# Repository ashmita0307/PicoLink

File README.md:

# PicoLink
An RP2040-based project for VGA graphics generation and USB composite device implementation.

## Table of Contents

  - [PicoLink](#picolink)
  - [Table of Contents](#table-of-contents)
  - [About The Project](#about-the-project)
  - [Features](#features)
  - [Project Workflow](#project-workflow)
  - [Hardware Used](#hardware-used)
  - [Breadboard Testing](#breadboard-testing)
  - [PCB Model](#pcb-model)
  - [Software Used](#software-used)
  - [Future Work](#future-work)
  - [Contributors](#contributors)
  - [Resources](#resources)
  - [Acknowledgements](#acknowledgements)

## About The Project
**PicoLink** is an RP2040-based project focused on **VGA graphics generation** and **USB communication**. It uses **PIO and DMA** for efficient VGA output and implements a **USB composite device with HID and CDC interfaces**.

## Features

- VGA output using RP2040
- Custom VGA graphics library
- Increased color support
- PIO-based VGA signal generation
- DMA-assisted data transfer
- Custom PCB design
- Space Invaders game
- Pacman game
## Project Workflow

#### Research

* Understanding VGA standards, timing, and signal generation
* Studying the RP2040's PIO and DMA peripherals
* Reviewing existing VGA libraries and RP2040 implementations

#### VGA Graphics Development

* Implementing VGA signal generation using PIO
* Developing a custom VGA graphics library
* Implementing framebuffer-based graphics
* Increasing color support and optimizing memory usage
* Testing VGA output on a monitor

#### PCB Design

* Designing the PicoLink PCB around the RP2040
* Designing the VGA interface and USB connections
* Routing the PCB while considering signal integrity and hardware constraints
* Finalizing the PCB for manufacturing
#### USB Development

* Implementing USB HID functionality
* Implementing USB CDC communication
* Creating and understanding the required USB descriptors
* Integrating HID and CDC as a composite USB device

#### Game Development & Testing

* Developing **Sngpace Invaders & Pacman** using the custom VGA graphics library
* Integrating the game with the PicoLink hardware
* Testing VGA output, USB communication, and overall system performance
* Debugging and optimizing the final implementation

## Hardware Used

|     Components        |          Description          |
| --------------------- | ----------------------------- |
| [RP2040-Mitrocontroller](https://robu.in/product/raspberry-pi-pico/?gad_source=1&gad_campaignid=19974686076&gbraid=0AAAAADvLFWc_9GsTRABB0vDtC2DQhwOhp&gclid=CjwKCAjwqJXUBhBNEiwA8BgG7vailV2Hy5Y_-Ko3vAaZAEXPT5CyTGmnKPxanKmfuWqEnSS08VfShBoCNk0QAvD_BwE)           | Microcontroller |
| [15-Pin VGA Connector](https://robu.in/product/x0615ft7b1-xkb-15p-female-d-sub-3-d-sub-vga-connectors-rohs/)  | VGA-connector |
| [33O ohm Resistors](https://robu.in/product/330-ohm-1-4w-1206-surface-mount-chip-resistor-pack-of-100/?gad_source=1&gad_campaignid=17427802703&gbraid=0AAAAADvLFWfZ2mYmii2USnEMQ98Oe9FQ_&gclid=CjwKCAjwqJXUBhBNEiwA8BgG7kQjg_4zEpnGfV_3AsnYPpfzbiUg2oPFK-0IBOd3eiSTI_ayuLDsIhoC2dwQAvD_BwE/) | Resistor |

## Breadboard Testing
- View of Breadboard VGA Connections:   

## PCB Model

- View of the PCB Model front and back:       
<table>
  <tr>
    <td align="center">
      
    </td>
    <td align="center">
      
    </td>
  </tr>
</table>

- View of the PCB Routing - front and back:      

<table>
  <tr>
    <td align="center">
      
    </td>
    <td align="center">
      
    </td>
  </tr>
</table>

## Software Used 

- PCB Design - [KiCad 10.0.5](https://www.kicad.org/)
- Software development kit for RP2040 - [Raspberry Pi Pico SDK](https://github.com/raspberrypi/pico-sdk) 

## Future Work
- [ ] Develop a more memory-efficient rendering system
- [ ] Develop more games/examples using the custom graphics library

## Contributors
- [Ashmita Subramanian](https://github.com/ashmita0307)
- [Mohd Aasim](https://github.com/Mohdaasim18)

## Resources

- [razorArnov Github Repository](https://github.com/razorArnov/PICO-VGA-BOARD.git)
- [Phil's lab Kicad Playlist](https://www.youtube.com/watch?v=O-zNn5k5Bn4)
- [Mikeshah's C Programming playlist](https://www.youtube.com/playlist?list=PLvv0ScY6vfd8M-Mi_Vyrg7KgISTW3Sklt)

## Acknowledgements 
- [SRA VJTI](https://sravjti.in/) Eklavya 2026
-[https://github.com/razorArnov/PICO-VGA-BOARD]
- Special thanks to our mentors [Omkar Nanajkar](https://github.com/nomkar24), [Moksh Panicker](https://github.com/moxybaba), and all the seniors at SRA, VJTI for their constant support and guidance throughout the project.

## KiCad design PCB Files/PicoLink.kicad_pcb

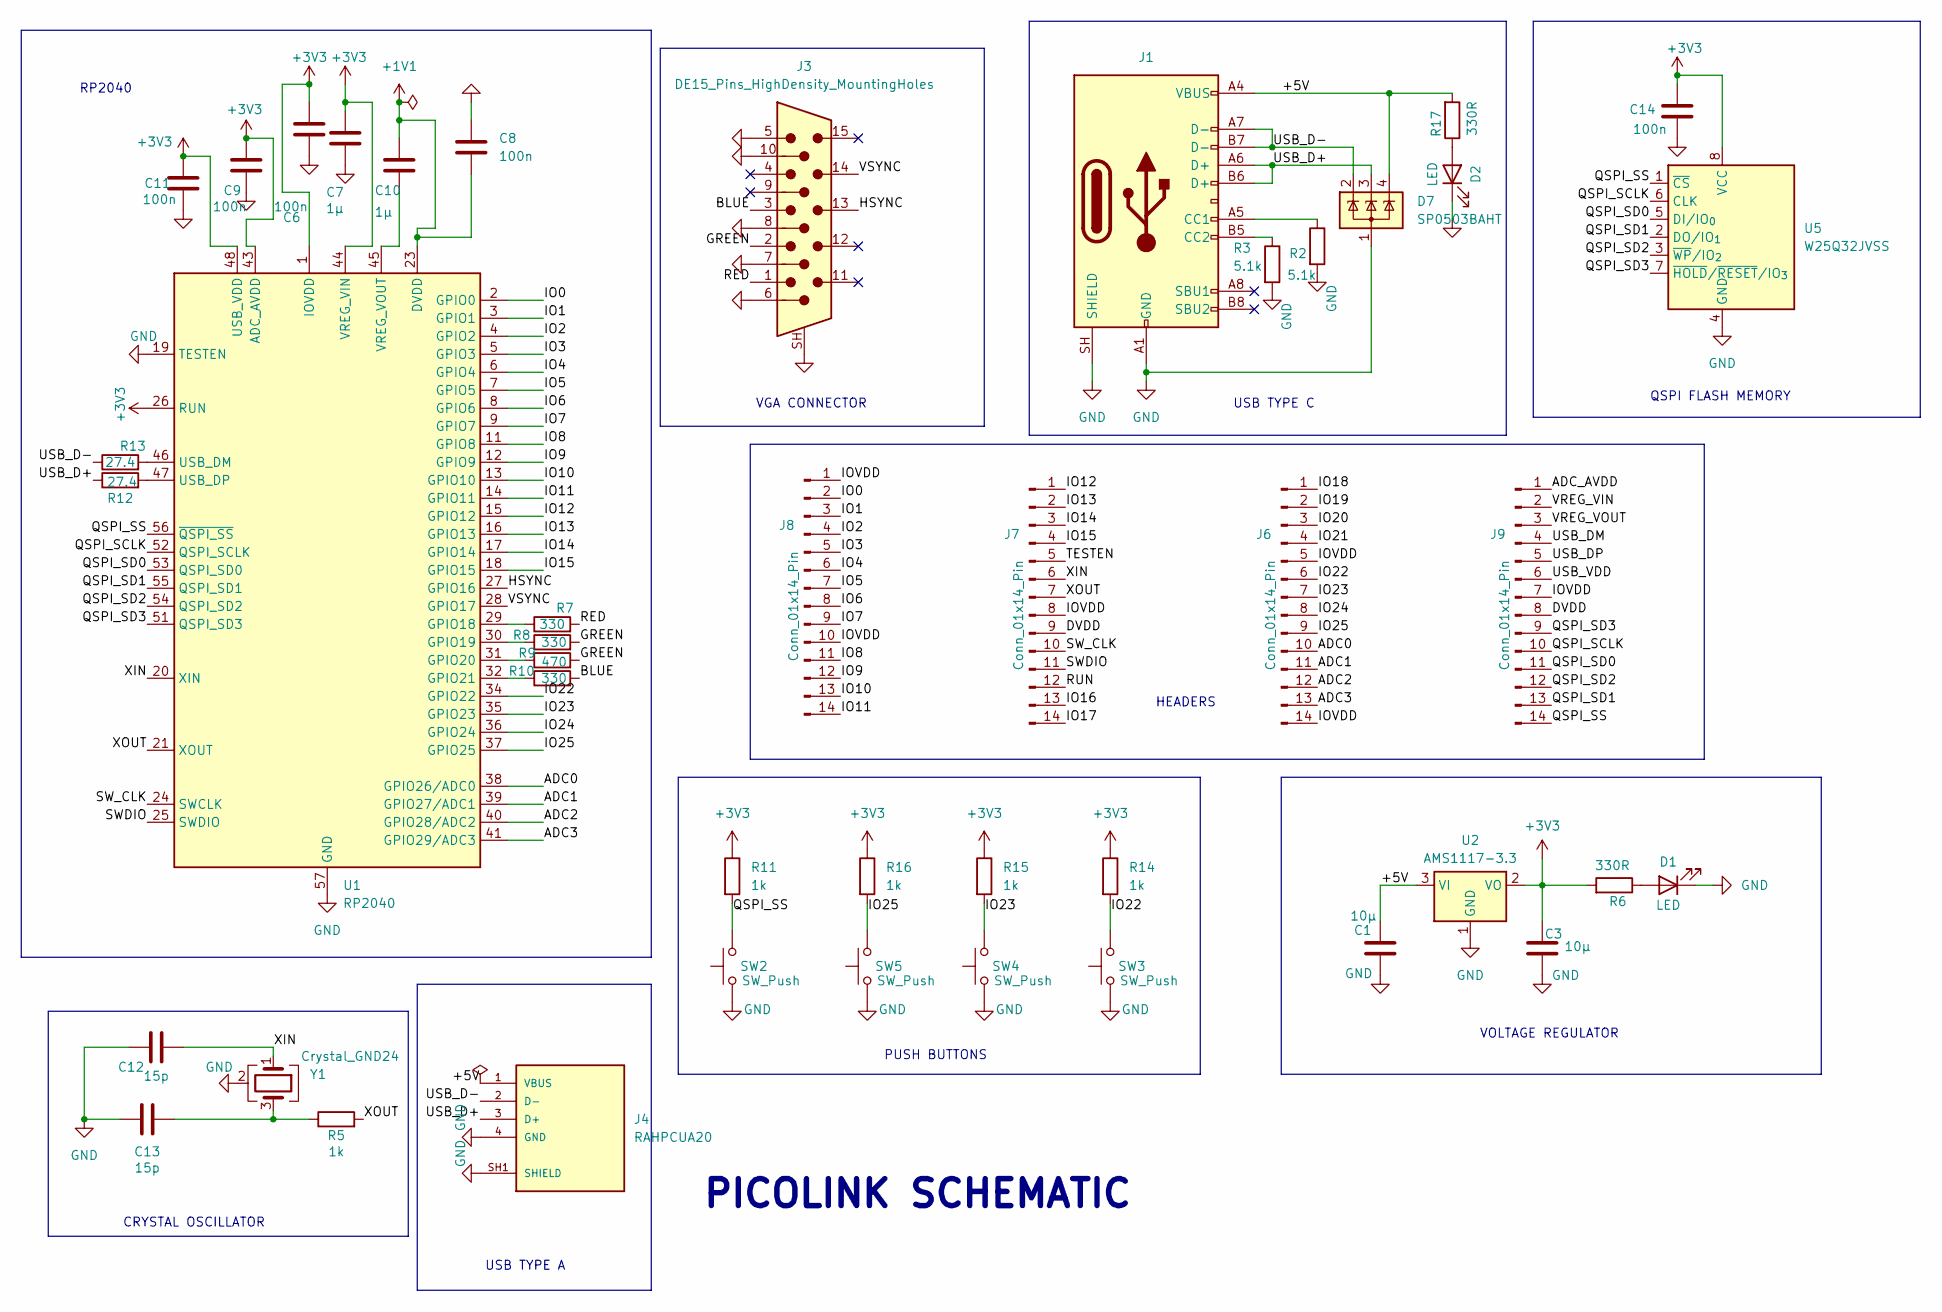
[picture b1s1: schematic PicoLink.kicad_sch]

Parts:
C1, C3: 10µ; C_0805_2012Metric
C6, C8, C9, C11, C14: 100n; C_0805_2012Metric
C7, C10: 1µ; C_0805_2012Metric
C12, C13: 15p; C_0805_2012Metric
D1, D2: LED; LED_0805_2012Metric
D7: SP0503BAHT; SOT-143
J1: USB_C_Receptacle_USB2.0_16P; USB_C_Receptacle_GCT_USB4105-xx-A_16P_TopMnt_Horizontal
J3: DE15_Pins_HighDensity_MountingHoles; DSUB-15-HD_Socket_Horizontal_P2.29x1.90mm_EdgePinOffset3.03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
J4: RAHPCUA20; USB_A_TE_292303-7_Horizontal; PARTREV A
J6, J7, J8, J9: Conn_01x14_Pin; PinHeader_1x14_P1.27mm_Vertical
R2, R3: 5.1k; R_0805_2012Metric
R5, R11, R14, R15, R16: 1k; R_0805_2012Metric
R6, R17: 330R; R_0805_2012Metric
R7, R8, R10: 330; R_0805_2012Metric
R9: 470; R_0805_2012Metric
R12, R13: 27.4; R_0805_2012Metric
SW2, SW3, SW4, SW5: SW_Push; SW_SPST_B3U-1000P
U1: RP2040; QFN-56-1EP_7x7mm_P0.4mm_EP3.2x3.2mm
U2: AMS1117-3.3; SOT-223-3_TabPin2
U5: W25Q32JVSS; SOIC-8_5.3x5.3mm_P1.27mm
Y1: Crystal_GND24; Crystal_SMD_Abracon_ABM8AIG-4Pin_3.2x2.5mm

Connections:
+1V1: C8.2, C10.1, U1.23 (DVDD), U1.50 (DVDD)
+3V3: C3.1, C6.1, C7.1, C9.1, C11.1, C14.1, R6.2, R11.1, R14.1, R15.1, R16.1, U1.1 (IOVDD), U1.10 (IOVDD), U1.22 (IOVDD), U1.26 (RUN), U1.33 (IOVDD), U1.42 (IOVDD), U1.43 (ADC_AVDD), U1.44 (VREG_VIN), U1.48 (USB_VDD), U1.49 (IOVDD), U2.2 (VO), U5.8 (VCC)
/+5V: C1.1, D7.4 (K), J1.A4 (VBUS), J1.A9 (VBUS), J1.B4 (VBUS), J1.B9 (VBUS), J4.1 (VBUS), R17.2, U2.3 (VI)
/ADC0: J6.10, U1.38 (GPIO26/ADC0)
/ADC1: J6.11, U1.39 (GPIO27/ADC1)
/ADC2: J6.12, U1.40 (GPIO28/ADC2)
/ADC3: J6.13, U1.41 (GPIO29/ADC3)
/ADC_AVDD: J9.1
/BLUE: J3.3, R10.2
/DVDD: J7.9, J9.8
/GREEN: J3.2, R8.2, R9.2
/HSYNC: J3.13, U1.27 (GPIO16)
/IO0: J8.2, U1.2 (GPIO0)
/IO1: J8.3, U1.3 (GPIO1)
/IO2: J8.4, U1.4 (GPIO2)
/IO3: J8.5, U1.5 (GPIO3)
/IO4: J8.6, U1.6 (GPIO4)
/IO5: J8.7, U1.7 (GPIO5)
/IO6: J8.8, U1.8 (GPIO6)
/IO7: J8.9, U1.9 (GPIO7)
/IO8: J8.11, U1.11 (GPIO8)
/IO9: J8.12, U1.12 (GPIO9)
/IO10: J8.13, U1.13 (GPIO10)
/IO11: J8.14, U1.14 (GPIO11)
/IO12: J7.1, U1.15 (GPIO12)
/IO13: J7.2, U1.16 (GPIO13)
/IO14: J7.3, U1.17 (GPIO14)
/IO15: J7.4, U1.18 (GPIO15)
/IO16: J7.13
/IO17: J7.14
/IO18: J6.1
/IO19: J6.2
/IO20: J6.3
/IO21: J6.4
/IO22: J6.6, R14.2, SW3.2, U1.34 (GPIO22)
/IO23: J6.7, R15.2, SW4.2, U1.35 (GPIO23)
/IO24: J6.8, U1.36 (GPIO24)
/IO25: J6.9, R16.2, SW5.2, U1.37 (GPIO25)
/IOVDD: J6.5, J6.14, J7.8, J8.1, J8.10, J9.7
/QSPI_SCLK: J9.10, U1.52 (QSPI_SCLK), U5.6 (CLK)
/QSPI_SD0: J9.11, U1.53 (QSPI_SD0), U5.5 (DI/IO_{0})
/QSPI_SD1: J9.13, U1.55 (QSPI_SD1), U5.2 (DO/IO_{1})
/QSPI_SD2: J9.12, U1.54 (QSPI_SD2), U5.3 (~WP/IO_{2})
/QSPI_SD3: J9.9, U1.51 (QSPI_SD3), U5.7 (~HOLD/~RESET/IO_{3})
/QSPI_SS: J9.14, R11.2, SW2.2, U1.56 (~QSPI_SS), U5.1 (~CS)
/RED: J3.1, R7.2
/RUN: J7.12
/SWDIO: J7.11, U1.25 (SWDIO)
/SW_CLK: J7.10, U1.24 (SWCLK)
/TESTEN: J7.5
/USB_D+: D7.3 (K), J1.A6 (D+), J1.B6 (D+), J4.3 (D+), R12.1
/USB_D-: D7.2 (K), J1.A7 (D-), J1.B7 (D-), J4.2 (D-), R13.1
/USB_DM: J9.4
/USB_DP: J9.5
/USB_VDD: J9.6
/VREG_VIN: J9.2
/VREG_VOUT: J9.3
/VSYNC: J3.14, U1.28 (GPIO17)
/XIN: C12.2, J7.6, U1.20 (XIN), Y1.1
/XOUT: J7.7, R5.2, U1.21 (XOUT)
GND: C1.2, C3.2, C6.2, C7.2, C8.1, C9.2, C11.2, C12.1, C13.1, C14.2, D1.1 (K), D2.1 (K), D7.1 (A), J1.A1 (GND), J1.A12 (GND), J1.B1 (GND), J1.B12 (GND), J1.SH (SHIELD), J3.5, J3.6, J3.7, J3.8, J3.10, J3.SH, J4.4 (GND), J4.SH1 (SHIELD), J4.SH2 (SHIELD), R2.2, R3.2, SW2.1, SW3.1, SW4.1, SW5.1, U1.19 (TESTEN), U1.57 (GND), U2.1 (GND), U5.4 (GND), Y1.2 (G), Y1.4 (G)
unnamed: C13.2, R5.1, Y1.3
unnamed: D1.2 (A), R6.1
unnamed: D2.2 (A), R17.1
unnamed: J1.A5 (CC1), R2.1
unnamed: J1.B5 (CC2), R3.1
unnamed: R7.1, U1.29 (GPIO18)
unnamed: R8.1, U1.30 (GPIO19)
unnamed: R9.1, U1.31 (GPIO20)
unnamed: R10.1, U1.32 (GPIO21)
unnamed: R13.2, U1.46 (USB_DM)
unnamed: R12.2, U1.47 (USB_DP)
unnamed: C10.2, U1.45 (VREG_VOUT)

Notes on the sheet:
QSPI FLASH MEMORY
USB TYPE A
VOLTAGE REGULATOR
HEADERS
RP2040
VGA CONNECTOR
CRYSTAL OSCILLATOR
USB TYPE C
PUSH BUTTONS
PICOLINK SCHEMATIC

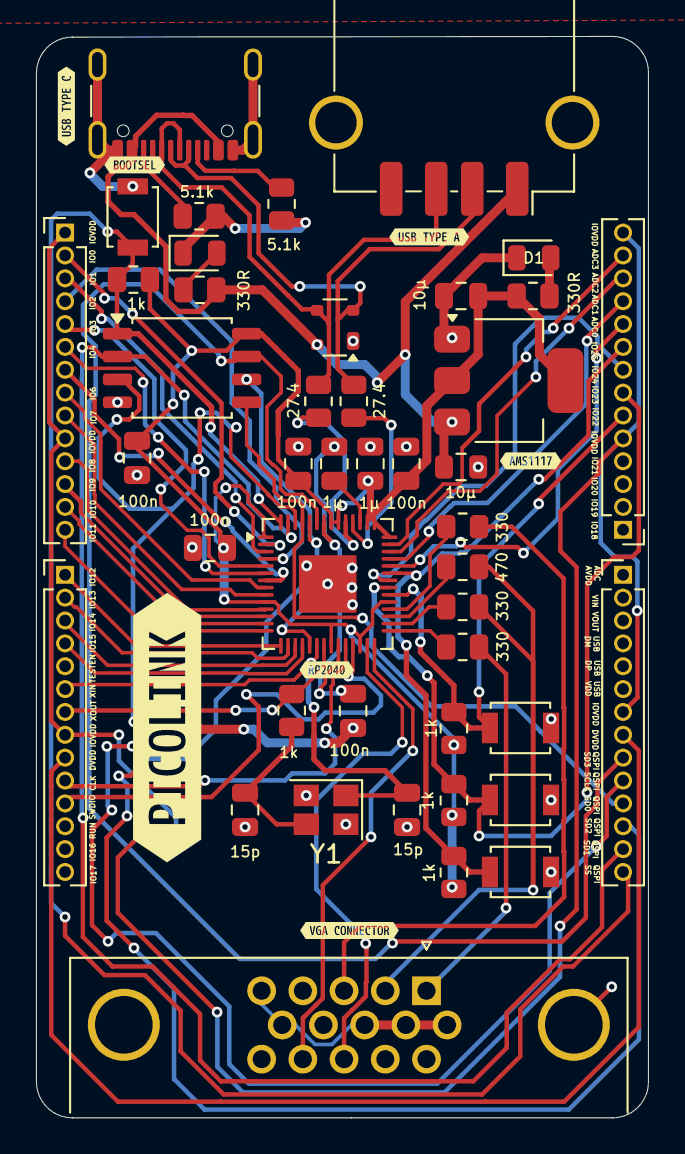
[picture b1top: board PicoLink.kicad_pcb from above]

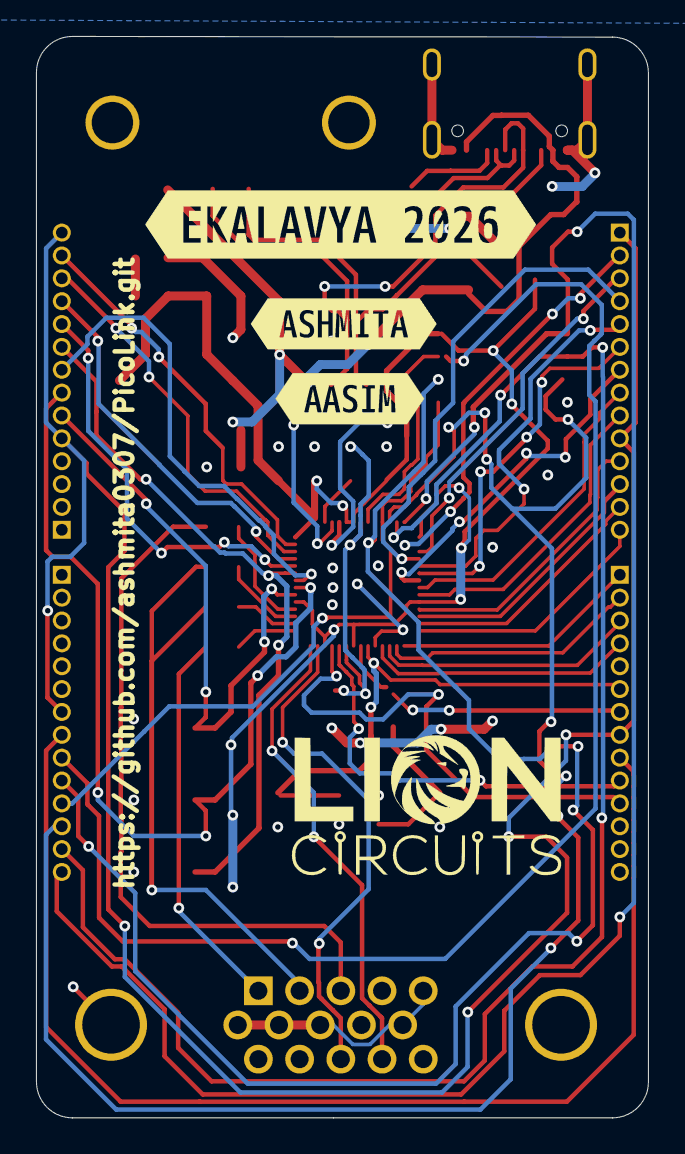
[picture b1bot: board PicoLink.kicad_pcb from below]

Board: 2 copper layers, 34.0 x 60.1 mm, 54 parts (3 on the bottom side), 59 nets.

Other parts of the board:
kibuzzard-6A7FFBEB: G***; kibuzzard-6A7FFBEB
kibuzzard-6A7FFF5E: G***; kibuzzard-6A7FFF5E
kibuzzard-6A7FFF8E: G***; kibuzzard-6A7FFF8E
kibuzzard-6A7FFF22: G***; kibuzzard-6A7FFF22
kibuzzard-6A7FFF38: G***; kibuzzard-6A7FFF38
kibuzzard-6A7FFFF4: G***; kibuzzard-6A7FFFF4
kibuzzard-6A81CC8C: G***; kibuzzard-6A81CC8C
kibuzzard-6A81CC73: G***; kibuzzard-6A81CC73
kibuzzard-6A81CC96: G***; kibuzzard-6A81CC96
kibuzzard-6A80000C: G***; kibuzzard-6A80000C
